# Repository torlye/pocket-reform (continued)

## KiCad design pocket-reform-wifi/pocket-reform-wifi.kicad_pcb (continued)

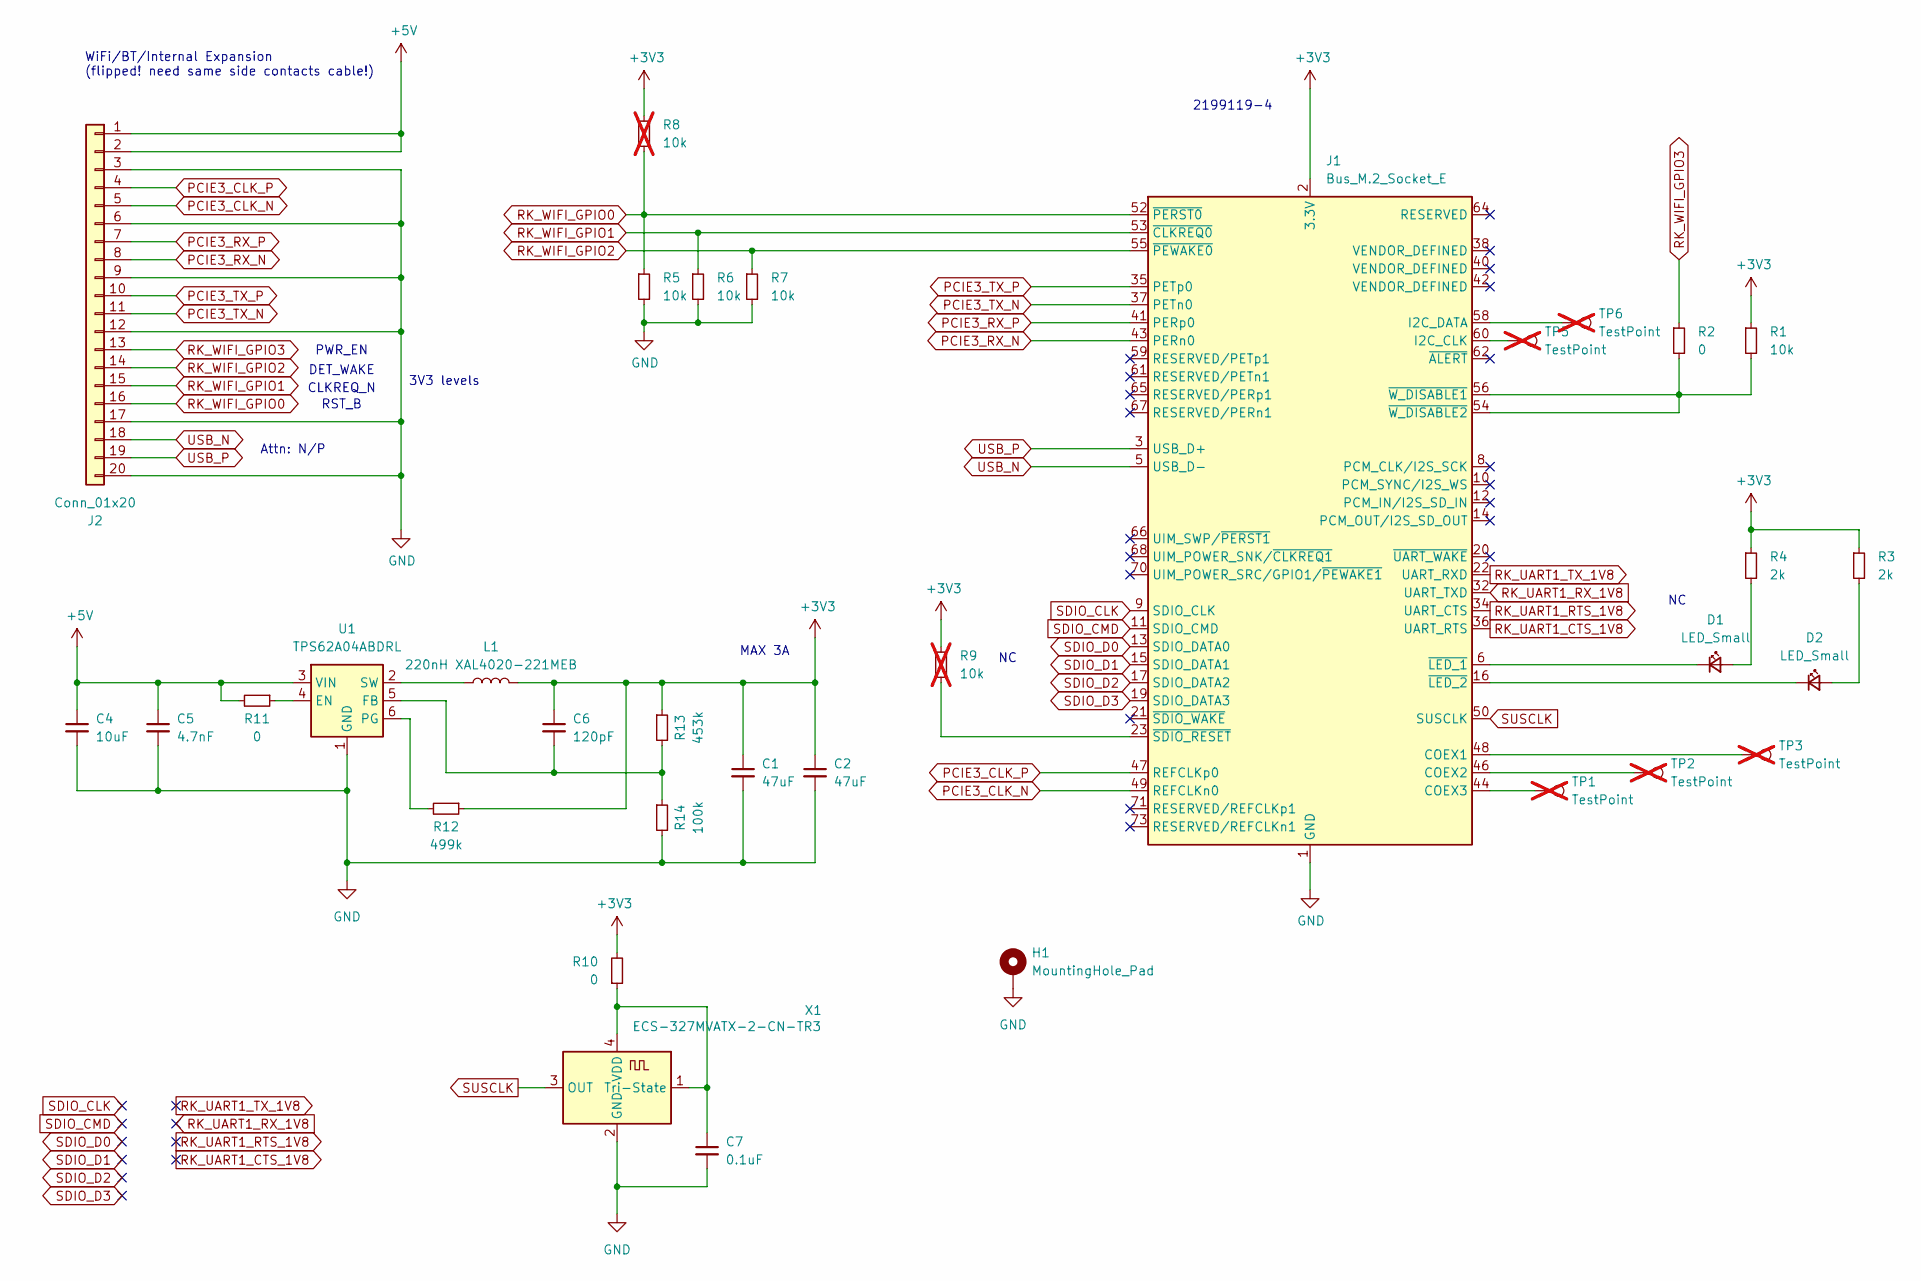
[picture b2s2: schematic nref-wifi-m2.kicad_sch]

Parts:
C1, C2: 47uF; C_1210_3225Metric; LCSC C84494
C4: 10uF; C_1210_3225Metric; LCSC C576517
C5: 4.7nF; C_0603_1608Metric; LCSC C85980
C6: 120pF; C_0603_1608Metric; LCSC C18438
C7: 0.1uF; C_0603_1608Metric; LCSC C77058
D1, D2: LED_Small; LED_0603_1608Metric; LCSC C5875723
H1: MountingHole_Pad; Mounting_Sinhoo_SMTSO20; LCSC C2916320
J1: Bus_M.2_Socket_E; TE_2199119-4; LCSC global sourcing
J2: Conn_01x20; Hirose_FH12-20S-0.5SH_1x20-1MP_P0.50mm_Horizontal; LCSC C596730
L1: 220nH XAL4020-221MEB; L_Coilcraft_XAL4020-XXX; LCSC C524578
R1, R5, R6, R7: 10k; R_0603_1608Metric; LCSC C98220
R2, R10, R11: 0; R_0603_1608Metric; LCSC C95177
R3, R4: 2k; R_0603_1608Metric; LCSC C105576
R8, R9: 10k; R_0603_1608Metric; LCSC C98220; not fitted
R12: 499k; R_0603_1608Metric; LCSC C131054
R13: 453k; R_0603_1608Metric; LCSC C2079749
R14: 100k; R_0603_1608Metric; LCSC C14675
TP1, TP2, TP3, TP5, TP6: TestPoint; TestPoint_Pad_D1.0mm; not fitted
U1: TPS62A04ABDRL; SOT-563; LCSC global sourcing
X1: ECS-327MVATX-2-CN-TR3; Oscillator_SMD_ECS_2520MV-xxx-xx-4Pin_2.5x2.0mm; LCSC C5375606

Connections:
+3V3: C1.1, C2.1, C6.1, J1.2 (3.3V), J1.4 (3.3V), J1.72 (3.3V), J1.74 (3.3V), L1.2, R1.1, R3.1, R4.1, R8.1, R9.1, R10.2, R12.1, R13.1
+5V: C4.1, C5.1, J2.1, J2.2, R11.2, U1.3 (VIN)
GND: C1.2, C2.2, C4.2, C5.2, C7.2, H1.1, J1.1 (GND), J1.7 (GND), J1.18 (GND), J1.33 (GND), J1.39 (GND), J1.45 (GND), J1.51 (GND), J1.57 (GND), J1.63 (GND), J1.69 (GND), J1.75 (GND), J2.3, J2.6, J2.9, J2.12, J2.17, J2.20, R5.2, R6.2, R7.2, R14.2, U1.1 (GND), X1.2 (GND); also elsewhere on the board
unnamed: D1.2 (A), R4.2
unnamed: D1.1 (K), J1.6 (~LED_1)
unnamed: D2.2 (A), R3.2
unnamed: D2.1 (K), J1.16 (~LED_2)
unnamed: J1.48 (COEX1), TP3.1
unnamed: J1.46 (COEX2), TP2.1
unnamed: J1.44 (COEX3), TP1.1
unnamed: J1.60 (I2C_CLK), TP5.1
unnamed: J1.58 (I2C_DATA), TP6.1
unnamed: J1.23 (~SDIO_RESET), R9.2
unnamed: J1.54 (~W_DISABLE2), J1.56 (~W_DISABLE1), R1.2, R2.2
unnamed: R11.1, U1.4 (EN)
unnamed: C6.2, R13.2, R14.1, U1.5 (FB)
unnamed: R12.2, U1.6 (PG)
unnamed: L1.1, U1.2 (SW)
unnamed: C7.1, R10.1, X1.1 (Tri-State), X1.4 (VDD)
PCIE3_CLK_N: J1.49 (REFCLKn0), J2.5
PCIE3_CLK_P: J1.47 (REFCLKp0), J2.4
PCIE3_RX_N: J1.43 (PERn0), J2.8
PCIE3_RX_P: J1.41 (PERp0), J2.7
PCIE3_TX_N: J1.37 (PETn0), J2.11
PCIE3_TX_P: J1.35 (PETp0), J2.10
RK_UART1_CTS_1V8: J1.36 (UART_RTS)
RK_UART1_RTS_1V8: J1.34 (UART_CTS)
RK_UART1_RX_1V8: J1.32 (UART_TXD)
RK_UART1_TX_1V8: J1.22 (UART_RXD)
RK_WIFI_GPIO0: J1.52 (~PERST0), J2.16, R5.1, R8.2
RK_WIFI_GPIO1: J1.53 (~CLKREQ0), J2.15, R6.1
RK_WIFI_GPIO2: J1.55 (~PEWAKE0), J2.14, R7.1
RK_WIFI_GPIO3: J2.13, R2.1
SDIO_CLK: J1.9 (SDIO_CLK)
SDIO_CMD: J1.11 (SDIO_CMD)
SDIO_D0: J1.13 (SDIO_DATA0)
SDIO_D1: J1.15 (SDIO_DATA1)
SDIO_D2: J1.17 (SDIO_DATA2)
SDIO_D3: J1.19 (SDIO_DATA3)
SUSCLK: J1.50 (SUSCLK), X1.3 (OUT)
USB_N: J1.5 (USB_D-), J2.18
USB_P: J1.3 (USB_D+), J2.19

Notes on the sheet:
3V3 levels
RST_B
PWR_EN
2199119-4
WiFi/BT/Internal Expansion (flipped! need same side contacts cable!)
MAX 3A
DET_WAKE
CLKREQ_N
Attn: N/P

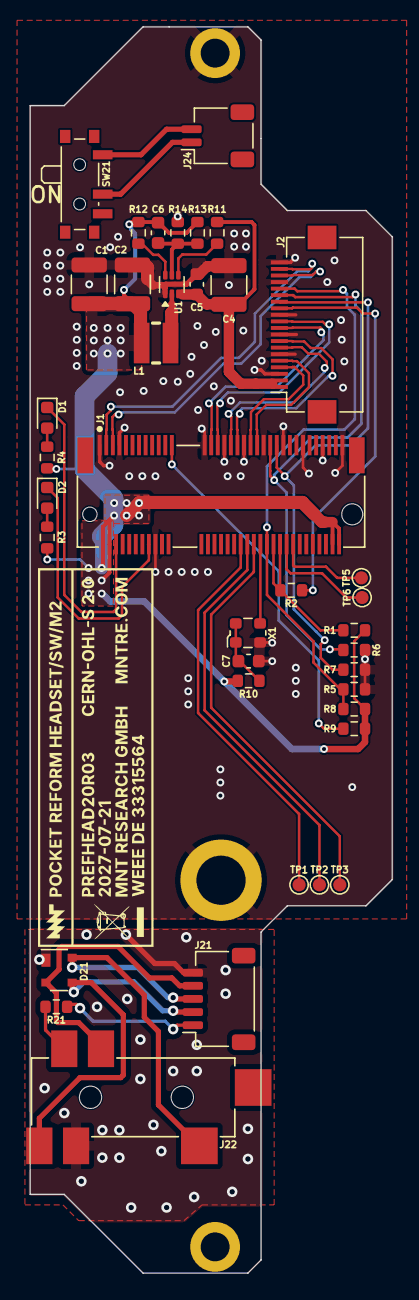
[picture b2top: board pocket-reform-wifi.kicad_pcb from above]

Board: 4 copper layers, 27.6 x 95.0 mm, 42 parts (0 on the bottom side), 40 nets.

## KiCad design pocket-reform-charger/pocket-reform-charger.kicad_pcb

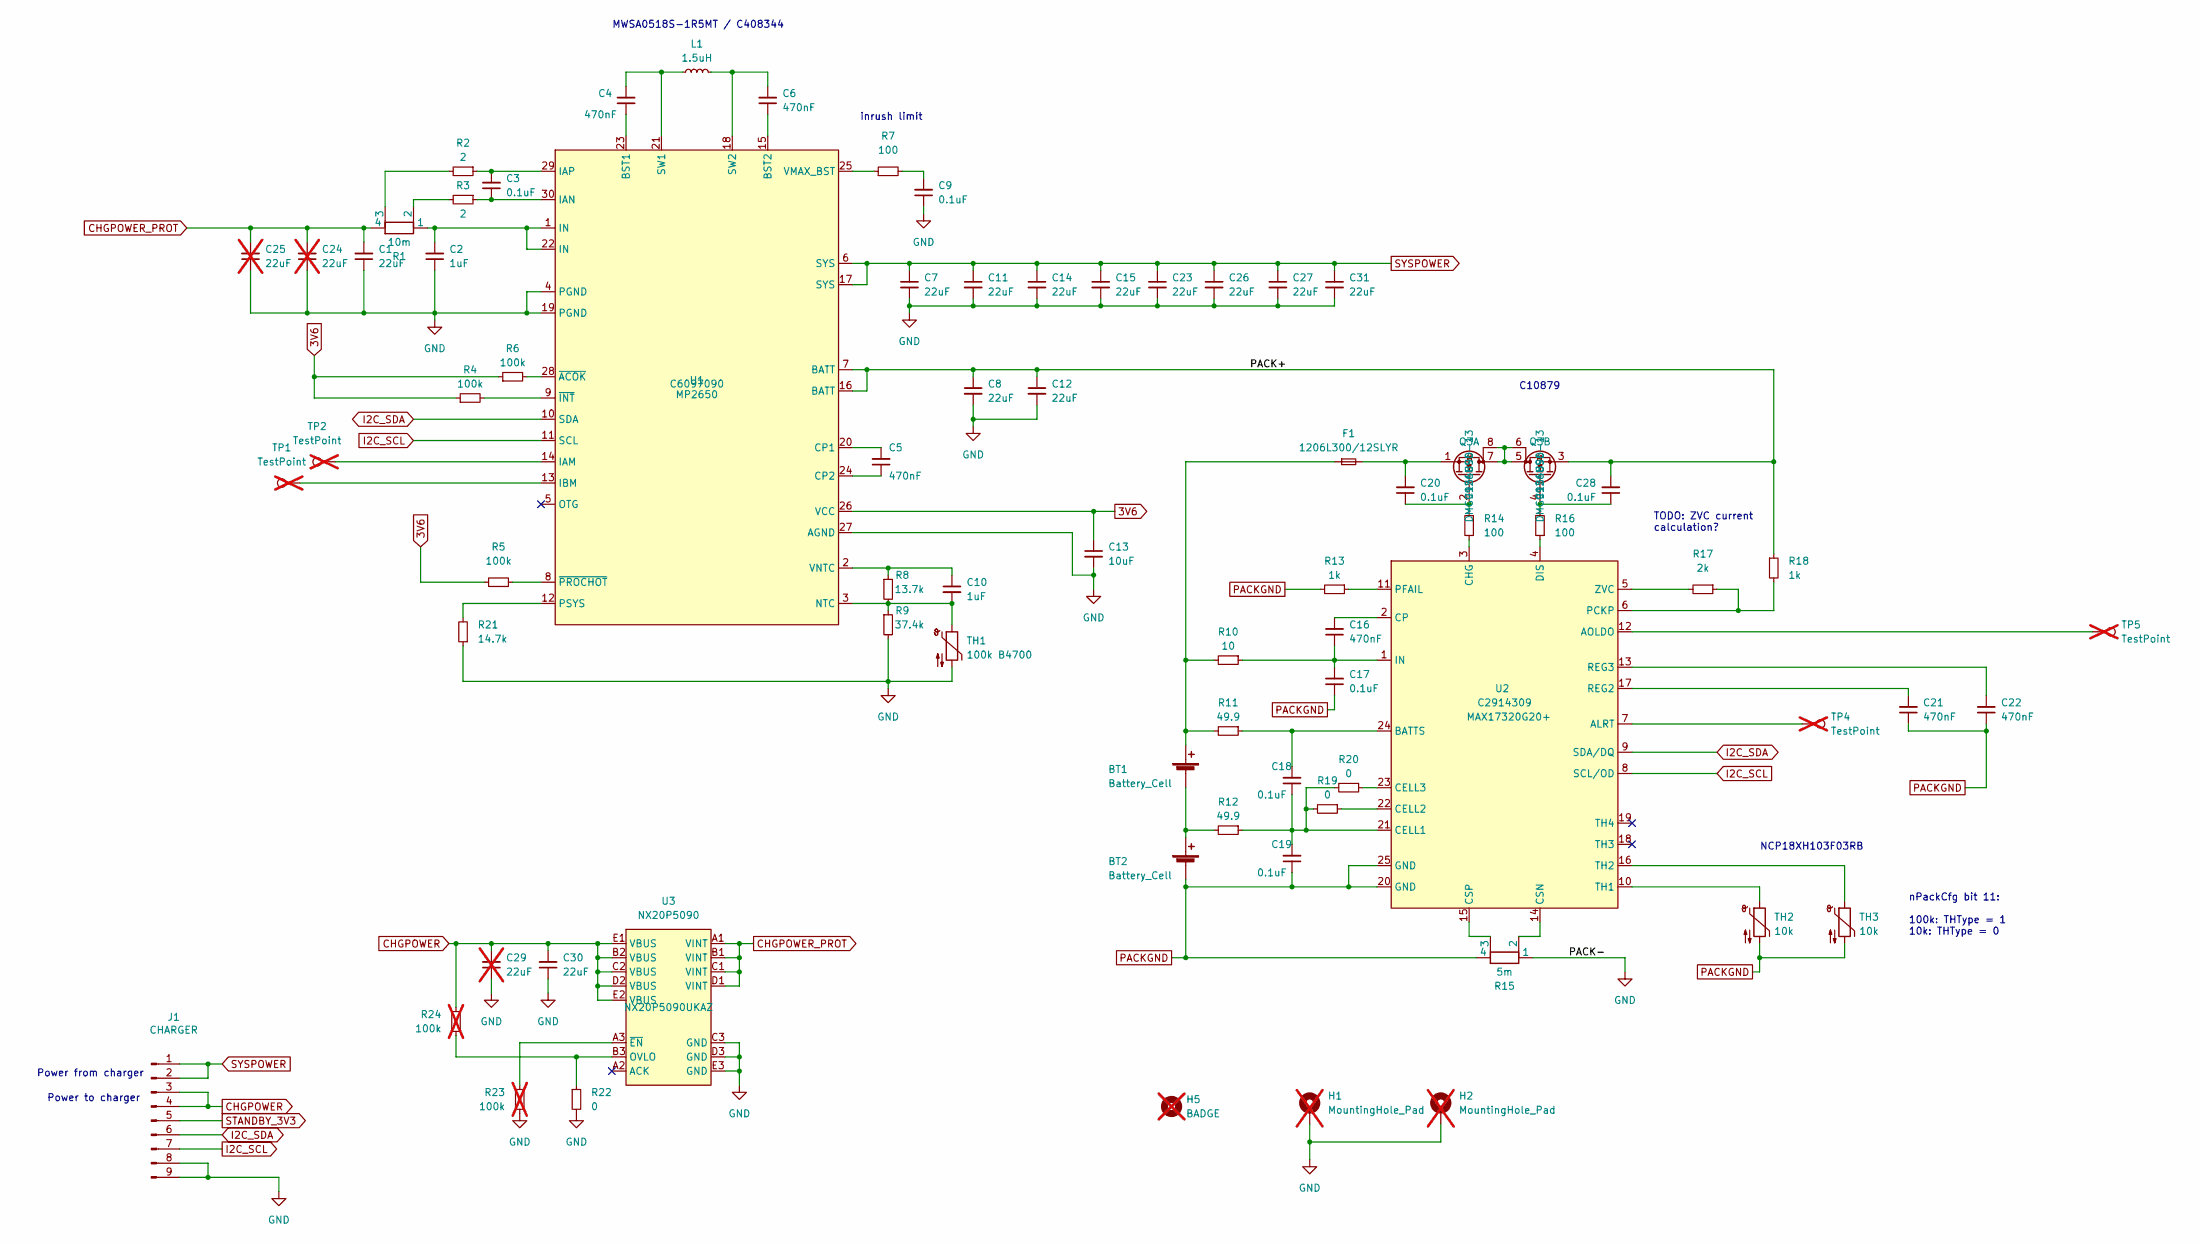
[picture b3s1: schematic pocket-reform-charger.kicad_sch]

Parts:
BT1, BT2: Battery_Cell; JST_PH_S2B-PH-SM4-TB_1x02-1MP_P2.00mm_Horizontal; LCSC C295747
C1, C7, C8, C11, C12, C14, C15, C23, C26, C27, C30, C31: 22uF; C_0805_2012Metric; LCSC C86816
C2, C10: 1uF; C_0603_1608Metric; LCSC C15849
C3, C9, C17, C18, C19, C20, C28: 0.1uF; C_0603_1608Metric; LCSC C14663
C4, C5, C6, C16, C21, C22: 470nF; C_0603_1608Metric; LCSC C2905413
C13: 10uF; C_0603_1608Metric; LCSC C386081
C24, C25, C29: 22uF; C_0805_2012Metric; LCSC C86816; not fitted
F1: 1206L300/12SLYR; Fuse_1206_3216Metric; LCSC C1512052
H1, H2: MountingHole_Pad; MountingHole_2.2mm_M2_Pad; not fitted
H5: BADGE; pocket-reform-charger-badge; not fitted
J1: CHARGER; JST_PH_S9B-PH-SM4-TB_1x09-1MP_P2.00mm_Horizontal; LCSC C395365
L1: 1.5uH; L_Sunlord_MWSA0518_5.4x5.2mm; LCSC C408344
Q3: Q_Dual_NMOS_S1G1S2G2D2D2D1D1; SOIC-8_3.9x4.9mm_P1.27mm; LCSC C154896
R1: 10m; R_1206_3216Metric_Kelvin; LCSC C2961483
R2, R3: 2; R_0603_1608Metric; LCSC C22977
R4, R5, R6: 100k; R_0603_1608Metric; LCSC C189597
R7, R14, R16: 100; R_0603_1608Metric; LCSC C384296
R8: 13.7k; R_0603_1608Metric; LCSC C22793
R9: 37.4k; R_0603_1608Metric; LCSC C23033
R10: 10; R_0603_1608Metric; LCSC C22859
R11, R12: 49.9; R_1206_3216Metric; LCSC C4014562
R13, R18: 1k; R_0603_1608Metric; LCSC C112433
R15: 5m; R_1206_3216Metric_Kelvin; LCSC C2988648
R17: 2k; R_0603_1608Metric; LCSC C163843
R19, R20, R22: 0; R_0603_1608Metric
R21: 14.7k; R_0603_1608Metric; LCSC C22874
R23, R24: 100k; R_0603_1608Metric; LCSC C189597; not fitted
TH1: 100k B4700; R_0603_1608Metric; LCSC C14663
TH2, TH3: 10k; R_0603_1608Metric; LCSC C13564
TP1, TP2, TP4, TP5: TestPoint; TestPoint_Pad_1.0x1.0mm; not fitted
U1: MP2650; MP2762A; LCSC C6097090
U2: MAX17320G20+; QFN-24-1EP_4x4mm_P0.5mm_EP2.65x2.65mm_ThermalVias; LCSC C2914309
U3: NX20P5090; NXP_NX20P5090; LCSC C2802659

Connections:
3V6: C13.1, R4.1, R5.1, R6.1, U1.26 (VCC)
/PACK+: C8.1, C12.1, C28.2, Q3.3 (S), R18.1, U1.7 (BATT), U1.16 (BATT)
CHGPOWER: C29.2, C30.2, J1.3, J1.4, R24.2, U3.B2 (VBUS), U3.C2 (VBUS), U3.D2 (VBUS), U3.E1 (VBUS), U3.E2 (VBUS)
CHGPOWER_PROT: C1.2, C24.2, C25.2, R1.4, U3.A1 (VINT), U3.B1 (VINT), U3.C1 (VINT), U3.D1 (VINT)
GND: C1.1, C2.1, C7.2, C8.2, C9.1, C11.2, C12.2, C13.2, C14.2, C15.2, C23.2, C24.1, C25.1, C26.2, C27.2, C29.1, C30.1, C31.2, H1.1, H2.1, J1.8, J1.9, R9.2, R15.1, R21.1, R22.2, R23.1, TH1.2, U1.4 (PGND), U1.19 (PGND), U1.27 (AGND), U3.C3 (GND), U3.D3 (GND), U3.E3 (GND)
I2C_SCL: J1.7, U1.11 (SCL), U2.8 (SCL/OD)
I2C_SDA: J1.6, U1.10 (SDA), U2.9 (SDA/DQ)
unnamed: BT1.1 (+), F1.1, R10.2, R11.2
unnamed: BT1.2 (-), BT2.1 (+), R12.2
unnamed: C2.2, R1.1, U1.1 (IN), U1.22 (IN)
unnamed: C9.2, R7.2
unnamed: Q3.5 (D), Q3.6 (D), Q3.7 (D), Q3.8 (D)
unnamed: C20.1, Q3.2 (G), R14.2
unnamed: C20.2, F1.2, Q3.1 (S)
unnamed: C28.1, Q3.4 (G), R16.2
unnamed: R1.2, R3.2
unnamed: R1.3, R2.2
unnamed: C4.1, U1.23 (BST1)
unnamed: C6.1, U1.15 (BST2)
unnamed: C5.2, U1.20 (CP1)
unnamed: C5.1, U1.24 (CP2)
unnamed: TP2.1, U1.14 (IAM)
unnamed: C3.1, R3.1, U1.30 (IAN)
unnamed: C3.2, R2.1, U1.29 (IAP)
unnamed: TP1.1, U1.13 (IBM)
unnamed: C10.2, R8.2, R9.1, TH1.1, U1.3 (NTC)
unnamed: R21.2, U1.12 (PSYS)
unnamed: C4.2, L1.1, U1.21 (SW1)
unnamed: C6.2, L1.2, U1.18 (SW2)
unnamed: R7.1, U1.25 (VMAX_BST)
unnamed: C10.1, R8.1, U1.2 (VNTC)
unnamed: R6.2, U1.28 (~ACOK)
unnamed: R4.2, U1.9 (~INT)
unnamed: R5.2, U1.8 (~PROCHOT)
unnamed: TP4.1, U2.7 (ALRT)
unnamed: TP5.1, U2.12 (AOLDO)
unnamed: C18.2, R11.1, U2.24 (BATTS)
unnamed: C18.1, C19.2, R12.1, R19.2, R20.2, U2.21 (CELL1)
unnamed: R19.1, U2.22 (CELL2)
unnamed: R20.1, U2.23 (CELL3)
unnamed: R14.1, U2.3 (CHG)
unnamed: C16.2, U2.2 (CP)
unnamed: R15.2, U2.14 (CSN)
unnamed: R15.3, U2.15 (CSP)
unnamed: R16.1, U2.4 (DIS)
unnamed: C16.1, C17.2, R10.1, U2.1 (IN)
unnamed: R17.1, R18.2, U2.6 (PCKP)
unnamed: R13.1, U2.11 (PFAIL)
unnamed: C21.2, U2.17 (REG2)
unnamed: C22.2, U2.13 (REG3)
unnamed: TH2.1, U2.10 (TH1)
unnamed: TH3.1, U2.16 (TH2)
unnamed: R17.2, U2.5 (ZVC)
unnamed: R22.1, R24.1, U3.B3 (OVLO)
unnamed: R23.2, U3.A3 (~EN)
PACKGND: BT2.2 (-), C17.1, C19.1, C21.1, C22.1, R13.2, R15.4, TH2.2, TH3.2, U2.20 (GND), U2.25 (GND)
STANDBY_3V3: J1.5
SYSPOWER: C7.1, C11.1, C14.1, C15.1, C23.1, C26.1, C27.1, C31.1, J1.1, J1.2, U1.6 (SYS), U1.17 (SYS)

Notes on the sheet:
MWSA0518S-1R5MT / C408344
TODO: ZVC current calculation?
C10879
NCP18XH103F03RB
inrush limit
Power from charger
nPackCfg bit 11: 100k: THType = 1 10k: THType = 0
Power to charger

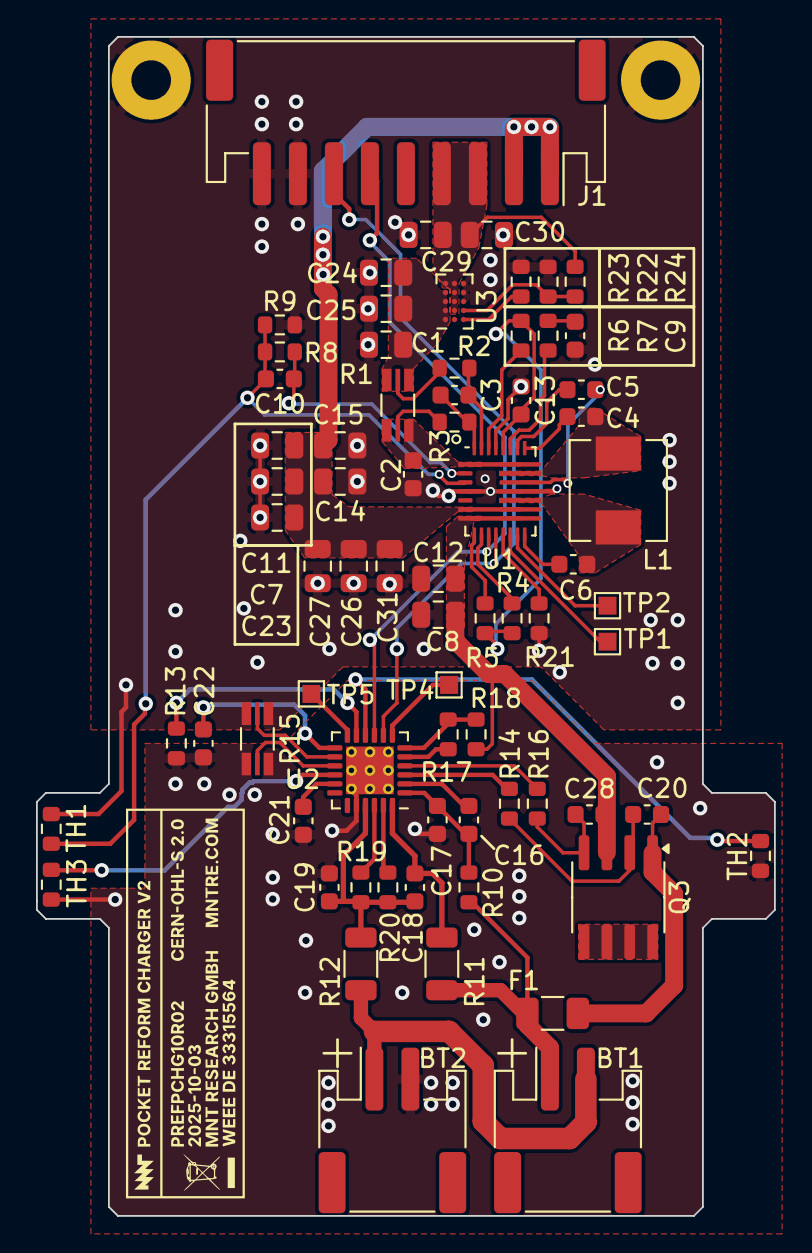
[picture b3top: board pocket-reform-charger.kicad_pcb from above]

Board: 4 copper layers, 41.0 x 65.5 mm, 74 parts (0 on the bottom side), 57 nets.

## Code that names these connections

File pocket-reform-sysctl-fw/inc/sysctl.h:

#ifndef _POCKET_SYSCTL_H
#define _POCKET_SYSCTL_H

#include <stdint.h>

#include "pico/stdlib.h"
#include "pico/binary_info.h"
#include "hardware/i2c.h"
#include "hardware/spi.h"
#include "hardware/irq.h"
#include "hardware/rtc.h"
#include "hardware/clocks.h"
#include "hardware/pwm.h"
#include "hardware/watchdog.h"
#include "hardware/structs/watchdog.h"
#include "hardware/structs/vreg_and_chip_reset.h"

// #define OTG_AS_5V // WARNING: defining this requires the hardware mod described in https://source.mnt.re/reform/pocket-reform/-/issues/3
// #define FACTORY_MODE // turn device on immediately after starting sysctl
#define ACM_ENABLED // usb serial control for debugging

#define FW_STRING1 "PREF1SYS"
#define FW_STRING2 "R1"

#define PIN_SDA 0
#define PIN_SCL 1

#define PIN_DISP_RESET 2
#define PIN_FLIGHTMODE 3
#define PIN_KBD_UART_TX 4
#define PIN_KBD_UART_RX 5
#define PIN_WOWWAN 6
// TODO: FIXME: DISP_2_PWM on v20
#define PIN_DISP_EN 7
#define PIN_SOM_MOSI 8
#define PIN_SOM_SS0 9
#define PIN_SOM_SCK 10
#define PIN_SOM_MISO 11
#define PIN_SOM_UART_TX 12
#define PIN_SOM_UART_RX 13
#define PIN_FUSB_INT 14
#define PIN_LED_B 15
#define PIN_LED_B_PWM_SLICE 7
#define PIN_LED_B_PWM_CHAN PWM_CHAN_B
#define PIN_LED_R 16
#define PIN_LED_R_PWM_SLICE 0
#define PIN_LED_R_PWM_CHAN PWM_CHAN_A
#define PIN_LED_G 17
#define PIN_MODEM_POWER 18
#define PIN_SOM_WAKE 19
#define PIN_MODEM_RESET 20
#define PIN_1V1_ENABLE 23
// 3V3_ENABLE on v10, kickstart (power on button) DP HPD output on v20
#define PIN_3V3_ENABLE 24
#define PIN_V20_DP_HPD 24
// 5V_ENABLE on v10, kickstart (power on button) input on v20
#define PIN_5V_ENABLE 25
#define PIN_PHONE_DPR 27
// USB_SRC/PWREN_LATCH on v10, USB_SRC1/USB_SRC2 on v20
#define PIN_USB_SRC_ENABLE 28
#define PIN_USB_SRC1_ENABLE 28
#define PIN_PWREN_LATCH 29
#define PIN_USB_SRC2_ENABLE 29
// NC on v10, EDL/USB bootloader enable on v20
#define PIN_USB_LOADER_SW 26

// FUSB302B USB-PD controller
#define FUSB_ADDR 0x22
// MAX17320 protector/balancer
// https://datasheets.maximintegrated.com/en/ds/MAX17320.pdf
#define MAX_ADDR1 0x36
#define MAX_ADDR2 0x0b
// MP2650 charger
// https://www.monolithicpower.com/en/documentview/productdocument/index/version/2/document_type/Datasheet/lang/en/sku/MP2650GV/document_id/9664/
#define MPS_ADDR 0x5c
#define TMUX_ADDR 0x54
// PCA9536DP GPIO extender (for USWITCHes)
#define PCA9536_ADDR 0x41
// PCA9557PW GPIO extender
#define PCA9557_ADDR 0x19
// TODO eeprom: 0x50/0x58

#define I2C_TIMEOUT (1000 * 20)

#define UART_ID uart1
#define BAUD_RATE 115200
#define DATA_BITS 8
#define STOP_BITS 1
#define PARITY UART_PARITY_NONE

#define BOOT_MAGIC_2 0xAA55F0F0
#define BOOT_MAGIC_3 0x0F0F55AA
#define BOOT_MAGIC_OFF (io_rw_32)(-1)

#define BATTERY_CAPACITY_MILLIAMP_HOURS 4000

#include "pd_com.h"

typedef struct battery_info_s
{
  bool som_is_powered;

  // reported by charger
  float battery_volts;
  float battery_amps;
  float input_volts;
  int cell_max_mah;

  // reported by balancer
  float cell1_volts;
  float cell2_volts;
  int charge_percentage;
  float time_to_empty;
  float gauge_avg_milliamps;
  float gauge_vpack;

  // metadata
  bool emergency_charge_necessary;
  bool print_pack_info;
  uint16_t max17320_devname;
  uint16_t ticks;
} battery_info_s;

#include "fusb302b.h"
#include "pd.h"
#include "max17320.h"
#include "mp2650.h"
#include "ext_gpio.h"

// Shared functions with communication classes
int mb_version();
void som_wake();
void turn_som_power_on();
void turn_som_power_off();
void set_display_v2_backlight_unlock(int on);
int get_display_v2_backlight_unlocked();
void set_display_backlight(int percent);
void set_display_backlight_freq(int freq);

void usb_host_5v_set(int port, int enable);
void set_usb_mode(int port, int mode);
void charger_enable_charge(int current);
void charger_disable_charge();
void enter_powersave(void);

// Recommended to call these around any i2c transactions
void sysctl_enable_irqs();
void sysctl_disable_irqs();

#endif

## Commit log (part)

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2024-08-26 scripts: update sysctl firmware from local build
2024-08-26 add fw update script to build artifacts
2024-09-03 refactor and toggle
2024-09-03 cleanup
2024-09-03 don't log voltage constantly
2024-09-03 restore prev build scripts
2024-09-03 increase time to wait for charger response
2024-09-03 vbus poll in its own state
2024-09-03 disable battery dump
2024-09-04 reduce state switch time, disable charger power on shtudown
2024-09-06 CI: build keyboard pocket-hid firmware
2024-09-06 keyboard: ensure pio_add_program is defined
2024-09-09 ci: fix building keyboard/pocket-hid firmware
2024-09-09 README: say what this repo holds
2024-09-09 ci: check USB reset descriptor strings are present in sysctl fw binary
2024-09-09 ci: split into multiple commands visible to GitLab
2024-09-16 install-fw-dependencies.sh: drop --depth on tinyusb
    Using --depth together with a git checkout $commit_id obviously fails
    when the remote HEAD moves. As long as tinyusb has no useful branches or
    tags, there is no good other way. For CI, maybe we could switch to a
    tarball download.
2024-09-22 sysctl: hook up fork of stdio_usb and tinusb_device
2024-09-22 Remove external copy of tinyusb
2024-10-12 sysctl: set USB manufactor and product name
2024-10-12 sysctl: describe us as self-powered USB device
    Vbus is tied to STANDBY_3V3, so the host has no control over us.
2024-10-15 sysctl: fix accidental long include paths
2024-10-15 sysctl: report as "Pocket Reform SysCtl 1.0"
    Increases USBD_DESC_STR_MAX to 25.
2024-10-16 sysctl: drop obsolete, broken USB descriptor check
2024-11-11 sysctl: use MNT USB IDs
2024-12-15 sysctl: set bcdDevice to lowest value
2024-12-15 sysctl: add fwupd DS-20 USB Descriptor
2024-12-15 scripts/generate-ds20: add --output parameter
2024-12-15 Import unmodified firmware_packager.py from fwupd contrib
2024-12-15 sysctl: properly fork reset interface from pico_stdio_usb
    The firmware side header (mntre_reset_priv.h) should in the future be
    shared between sysctl and hid. reset_interface.* maybe too.
2024-12-15 sysctl: always enable Reset interface
2024-12-15 firmware_packager: XML-escape data
2024-12-15 firmware_packager: allow reading release description from a file
2024-12-15 CI: use tag as MNTRE_FIRMWARE_VERSION
2025-01-01 fix comment
2025-01-01 fix shift key
2025-01-02 update-keyboard-firmware.sh: output helpful docs
2025-01-02 sysctl: extract USB reset code
2025-01-02 sysctl: extract USB IDs and DS20 defines into new headers
2025-01-02 sysctl: add source of guid
2025-01-02 pocket-hid: add fwupd and reset capability
2025-01-02 sysctl: stop requiring pico-extras
2025-01-05 hid: fix potential endless loop in uart rx; set watchdog to 1000ms; explicit uart configuration; send poweron twice
2025-01-06 kbd fw: use system-wide pico-sdk in /usr/src
2025-01-06 kbd fw: restore original trackball speed
2025-01-06 sysctl: support both display models at once
2025-01-06 kbd fw: use snprintf; use fw version from environment/build
2025-01-07 USB PD Rework
2025-01-07 Init battery data earlier
2025-01-07 pocket-hid: fix undeclared tusb_* functions
2025-01-07 sysctl: uart: track validity of cmd number argument
2025-01-07 sysctl: stop lying to the psu about the current we will draw
2025-01-07 sysctl: add missing newline
2025-01-07 display v2: limit brightness to 80%
2025-01-10 update-keyboard-firmware: fix file check
    Commit f9c0be3904a22308d53c33038c60ac3e8a9a01b1 changed the magic string.
2025-01-13 sysctl: clear PWREN_LATCH just before reset
    Avoid resetting the SOC if we are holding the power latch for displayv2 brightness.
2025-02-05 kbdtest: add helper script
2025-04-29 WIP update-sysctl-firmware.sh for a number of scenarios
2025-05-06 sysctl: respect charger-supplied current limit
2025-05-12 Sysctl fix reboot state
2025-05-22 pocket-reform-keyboard-fw/pocket-hid/flash.sh: be interactive
2025-05-30 WIP: port new spi handler from classic lpc
2025-05-30 sysctl-fw: fix SPI handling to match what the driver expects
2025-05-30 charger: v2 WIP
    * new 4 layer design
    * optimized current flow
    * better sense layout
    * actually have smth worthy of being called a ground plane
    missing:
    * NX20P5090UKAZ
2025-05-30 charger: add missing footprint library
2025-05-30 charger: add fp/sym-lib-table
2025-05-30 sysctl: update flash.sh
2025-05-30 sysctl: some indentation fixes
2025-06-05 add first version of new headset pcb with integrated m.2 key e wifi/bt slot
2025-06-07 install-fw-dependencies.sh: do not require apt 2.7.0 for the --update option
2025-06-09 sysctl: spi: don't talk to turned-off cpu
2025-06-09 pd_com: comment out potential endless loop
2025-06-09 sysctl: introduce 1sec watchdog reset
2025-06-09 fwupd: fix descriptions for cab packaging for release builds
2025-06-21 DONOTMERGE build anri kbd layout in CI
2025-06-23 sysctl-fw: bump watchdog reset to 10s timeout
2025-07-01 sysctl fw: fix release metadata for 20250623
2025-07-03 set PICO_SDK_PATH in build.sh scripts to the cloned repository
2025-07-20 remove idle backlight dimming
2025-07-24 CI: fix logical error
2025-09-07 sysctl: detect empty batteries and allow slow charge
    Otherwise recovery from empty batteries is impossible without turning off sysctl.
2025-09-07 hid: expand FWCAB_FIRMWARE_DESCRIPTION
2025-09-07 hid: add LVFS release notes
2025-09-20 kbd: add a hyper shortcut to show free (heap) memory
2025-09-20 sysctl: fix some printf formats (cppcheck)
2025-09-20 sysctl: fix cppcheck style issues
2025-09-20 bump pico sdk version for CI build to 2.2.0
2025-09-20 kbd/remote: remove unused variable (cppcheck)
2025-09-20 easter egg: remove unreachable condition (cppcheck)
2025-09-20 cppcheck and pico-sdk gcc disagree on bitness of unsigned int
2025-09-20 pocket doesn't use AVR anywhere
2025-09-20 keyboard-fw: remove dynamic allocation (strdup) of OLED strings (argh)
2025-09-20 cppcheck fix
2025-09-23 .gitlab-ci.yml: use build.sh scripts
    - avoid duplication of build instructions
    - make CI use the same scripts used for local development
    - use the same pico-sdk version for CI and local builds
    - follow the same trend already implemented in the other MNT projects:
    build logic moves from .gitlab-ci.yml to shell scripts called by
    .gitlab-ci.yml
2025-09-23 pocket-reform-{keyboard,sysctl}-fw/.../CMakeLists.txt: use ./pico-sdk git clone if PICO_SDK_PATH is not set
2025-09-27 Upload firmware builds to LVFS
    Skip the upload job on unprotected branches, and when the protected var
    is unavailable, like on forks.
2025-09-27 WIP: make all i2c calls time out
2025-09-27 sysctl: add timeout to SPI replies
2025-09-28 keyboard-fw: don't sleep_us in timer interrupt
2025-09-28 keyboard-fw: detect and sync to sysctl power state after reset
2025-09-28 lvfs-upload: show body on http errors
    Might be helpful in diagnosing the occasional HTTP 502 from lvfs.org.
2025-09-28 fw: move custom USB class driver registration
    Each firmware should be able to register its own custom class drivers, instead
    of mntre_reset defining the global callback for tinyusb.
2025-09-28 cppcheck: check pocket-reform-shared-fw too
2025-09-28 sysctl: avoid relocation error in debug builds
    Avoids this error from ld when building with -DCMAKE_BUILD_TYPE=Debug:
    ```
    /usr/lib/gcc/arm-none-eabi/14.2.1/../../../arm-none-eabi/bin/ld: CMakeFiles/sysctl.dir/src/pd_com.c.obj: in function `pd_tick':
    src/pd_com.c:271:(.text.pd_tick+0x17a): undefined reference to `pd_set_fusb_switches1'
    /usr/lib/gcc/arm-none-eabi/14.2.1/../../../arm-none-eabi/bin/ld: (pd_set_fusb_switches1): Unknown destination type (ARM/Thumb) in CMakeFiles/sysctl.dir/src/pd_com.c.obj
    src/pd_com.c:271:(.text.pd_tick+0x17a): dangerous relocation: unsupported relocation
2025-09-29 CI: sleep between LVFS uploads
    Per https://gitlab.com/fwupd/lvfs-website/-/issues/1037#note_2786314058
2025-10-02 pocket-reform-wifi: revision r2 with different inductor footprint
2025-10-02 pocket-reform-charger pcb v2 layout completed
    - layout finished by carson walls
    - initial new mp2650+nx20p5090 layout by f. schneider
    - final polishing by lucie l. hartmann
2025-10-03 charger v2: bom tweaks
2025-10-04 fusb_read_message: use fusb_read_buf instead of fusb_read_byte
2025-10-04 sysctl: remove fusb_read_byte
2025-10-04 sysctl: support USB2.0 USB-A devices better
2025-10-04 sysctl: restore OTG_AS_5V capability
    Debugging the OTG feature revealed that REG08h ends up with NTC_GCOMP_SEL=1,
    which is the after-reset default. Given we clearly set it to 0, I can only
    assume that the first read-back happens too soon. I do not like this
    explanation, but the change works.
2025-10-04 sysctl: keep ignoring INT line from fusb
    Looks like we can read everything we care about - in time - without the INT
    line. At least for now.
2025-10-04 sysctl: reduce fusb write traffic
    Stop writing defaults after RESET, stop clearing INTERRUPTB.
2025-10-04 sysctl: shorten print_src_fixed_pdo output
2025-10-04 sysctl: more serious
2025-10-04 sysctl: extract pd_comm_pd
2025-10-16 sysctl: have breathing charging indicator never be dark
    Instead go to 10% brightness as a minimum.
2025-10-16 Simplify GPIO initialization and keyboard scanning using masks
    The Pi Pico SDK allows for the configuration and manipulation of
    multiple GPIO pins simultaneously using GPIO masks. This changes GPIO
    initialization to use two new masks, one for keyboard columns (output)
    and one for keyboard rows (input), and clears keyboard columns during
    scan using another mask operation.
    This should not change any behavior and will affect runtime only
2025-10-21 hid: have brightness change slower
2025-10-21 hid: reduce OLED brightness
    Maximum is just too bright IMO.
2025-10-22 keyboard-fw: clean up global variables and functions
    - Remove several unused global variables in remote.c
    - Change some functions to static scope in main.c
    - Change remaining global variables to static scope in main.c,
    remote.c, menu.c, oled.c
2025-10-23 keyboard-fw: change the menu display system to a state machine
    The menu display system was previously a state machine in several
    variables; this change transitions it (pun) to a state machine with a
    single state variable, four well-defined states, and two ancillary
    data variables (unchanged).
2025-10-27 keyboard-fw: include a HACKING document for getting started
2025-10-28 keyboard-fw: reduce time that keyboard matrix is active
    The keyboard matrix was previously passing current through the final
    column during idle periods after the first keyboard poll following
    reset. This change brings column pins high for only about one
    microsecond, then reads all GPIO pins and checks the row pins
    individually from that single read.
2025-11-17 keyboard-fw: leds: add hue/saturation/brightness setting over USB
2025-11-18 Add new directory
2025-12-15 tref proto: on/off button
2025-12-18 first port to rp2350a (without usb hid yet)
2025-12-18 move pico_dsk_import stuff to lib
2025-12-18 restore USB HID function
2025-12-18 try to build keyboard v2 in CI
2025-12-28 sysctl/flash.sh: reduce wait time
    Might help to avoid unexpected reboots by having the sysctl be offline for a
    shorter amount of time.
    Also fail early if a called program fails.
2026-01-06 sysctl: factor PDO selection out
2026-01-06 sysctl: tidy up USB PD message "parser"
    Correctly identify most messages, incl. GoodCRC which we can ignore for now. Reply to Discover_Identity to improve handshaking with some (notably Apple) chargers.
2026-01-09 sysctl: enable mp2650 watchdog
2026-01-29 pocket keyboard 1.1 schematic and pcb mostly done
2026-02-02 PREF keyboard: V1.5-R1
2026-02-06 pref mainboard 1.5: schematic/routing progress
2026-02-09 pref mainboard v1.5 place+route progress
2026-02-13 sysctl-fw: add g and G commands for toggling GPIOs
2026-02-20 mb1.5: routing WIP
2026-02-26 mb1.5: small schematic updates
2026-02-26 mb1.5 WIP
2026-02-27 install-fw-dependencies: use patched version of pico-sdk that uses picolibc
2026-02-27 kbd1.5: add note in schematic
2026-03-06 WIP mb1.5 routing snapshot
2026-03-09 mb20: add missing 3d models
2026-03-09 WIP mb20 initial routing complete, and some silkscreen cleanup
2026-03-11 CI: tags test 1
2026-03-11 CI: tags test 2 (yaml is strange?)
2026-03-11 pocket reform mainboard 2.0 d-1 finished for export
2026-03-11 pocket reform mainboard 2.0 d-1 BOM fixes during sample order
2026-03-14 sysctl-fw: uart: silence some printfs, enable all powers on soc wake
2026-03-14 clean up code a bit
